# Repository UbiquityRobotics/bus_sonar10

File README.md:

# bus_sonar10

The Sonar10 board is used to drive up to 10 HC-SR04
sonar modules.

Currently, everything is located in the `rev_a` directory.

## Revision A

The revision A schematic is available as either
`bus_sonar10.pdf` or as `bus_sonar10.svg`.

Logic ground comes in on N1 (pins 3 and 4).  Logic
power comes in on N1 (pins 1 and 2.)  The logic power
is routed to C1, U2 (a LM2940-5.0), C4, C5, and R1.
The C4/R1 series combination is used to bring the
ESR of C5 to less than 1 ohm as required by the
LM2940 spec. sheet.  Capacitors C6, C7, C8, C9, and
C11 provide filter capacitors for the various IC's.

The MCP2562 CAN bus transceiver (U3) is connected to
CANH (N1 pin 5) and CANL (N1 pin 6).  In addition,
R6 and J1 can be used to enable a 120 ohm CAN bus
termination resistor.  VIO (U3 pin 5) is connected
to 5V since all digital signals on this board are
running at 5V.

The AND gate at U1A is used to or the signals from
the MCP2562 TXD (U3 pin 1) with the TXD signal on
the 3.3V FTDI USB serial cable (N2 pin 4).  R4 is
a 100K ohm pull resistor that pulls serial cable
high if no serial cable is plugged in.  (There should
be a similar 100K pull-up resistor on the MCP2662
to pull it high if the MCP2562 CAN bus transceiver
is not plugged in.  It was accidently left out.)
The output of the 74HCT08 and gate is directed to
RXD (U4 pin 2) of the ATmega328P.  The 74HCT08 is
used to level shift from 3.3V on the serial cable
up to 5V output on U1A.  (Note: in Rev. A the TXD
and RXD pins on U3 are accidentally swapped.)  Lastly,
the TXD output from the processor is sent to the R2/R3
voltage divider that takes the 0-5V signal down to 0-3V.

One other comment about the serial cable.  If a 5V FTDI
serial cable gets plugged into N2, nothing bad happens
because U1 has 5V tolerant inputs.

The reset signal is derived from RTS on the serial cable
(N2 pin 6.)  Normally, RTS on the serial cable idles
at 3.3V high, which is buffered through AND gate U1B
to 5V.  The othe end of C10 is pulled up to 5V through
10K resistor (R7).  Since both ends of C10 are at 5V,
C10 is discharged and has 0V across it.  When RTS goes
low, the output of U1B goes low.  This immediately pulls
the #RESET line low and that resets the processor on
its #RESET line (U4 pin 1).  Now R7 has 5V across it
and it starts to charge C10 up to 5V.  When downloading
is done, The serial cable signal RTS goes back high again.
This the causes the U1B AND output to go high (5V).
This causes the other end of C10 to attempt to pull
the #RESET line up to 10V (since C10 has 5V across it.)
Luckily the Schottky diode D1 to clamp the voltage
on the #RESET line to 5.2V and rapidly discharge C10
again.  Lastly, the button SW1 can be used to trigger
a reset as well.

(There was a theory that the AVR counter/timers could
be used to time the width of a pulse.  For this reason,
all sonar echos were run into the input pins of
5 (OC2B), 11 (OC0B), 12 (OC0A), 15 (OC1A), 16 (OC1B),
and 17 (OC2A).  Alas, this theory turned out to be
false.)

Order to support 10 sonars, pairs of echo return signals
from the HC-SR04 modules are combined using the 74HCT32
quad OR gate U5.  By using these 4 OR gates, the 10
sonar echos are directed to 6 input pins.  This is good
because 6 input pins are all that is available.

All the connections are summerized in the table below:
<BlockQuote>
  <Table Border="1">
    <TR>
      <TH RowSpan="2">Sonar</TH>
      <TH ColSpan="4">Trigger</TH>
      <TH ColSpan="7">Echo</TH>
    </TR><TR>
      <TH>Pin</TH>
      <TH>Arduino</TH>
      <TH>Port-Bit </TH>
      <TH>Conn-Pin</TH>
      <TH>Pin</TH>
      <TH>Arduino</TH>
      <TH>Counter</TH>
      <TH>Port-Bit</TH>
      <TH>PCINT</TH>
      <TH>Conn-Pin</TH>
    </TR><TR>
      <TD>0</TD>
      <TD>24</TD>
      <TD>A1</TD>
      <TD>PC1</TD>
      <TD>N3-5</TD>
      <TD RowSpan="2">15</TD>
      <TD RowSpan="2">D9</TD>
      <TD RowSpan="2">OC1A</TD>
      <TD RowSpan="2">PB1</TD>
      <TD RowSpan="2">PCINT1</TD>
      <TD>N3-3</TD>
    </TR><TR>
      <TD>1</TD>
      <TD>19</TD>
      <TD>D13</TD>
      <TD>PB5</TD>
      <TD>N3-13</TD>
      <TD>N3-11</TD>
    </TR><TR>
      <TD>2</TD>
      <TD>23</TD>
      <TD>A0</TD>
      <TD>PC0</TD>
      <TD>N3-21</TD>
      <TD>12</TD>
      <TD>D6</TD>
      <TD>OC0A</TD>
      <TD>PD6</TD>
      <TD>PCINT22</TD>
      <TD>N3-19</TD>
    </TR><TR>
      <TD>3</TD>
      <TD>18</TD>
      <TD>D12</TD>
      <TD>PB4</TD>
      <TD>N3-29</TD>
      <TD RowSpan="2">11</TD>
      <TD RowSpan="2">D5</TD>
      <TD RowSpan="2">OC0B</TD>
      <TD RowSpan="2">PD5</TD>
      <TD RowSpan="2">PCINT21</TD>
      <TD>N3-27</TD>
    </TR><TR>
      <TD>4</TD>
      <TD>14</TD>
      <TD>D8</TD>
      <TD>PB0</TD>
      <TD>N3-37</TD>
      <TD>N3-35</TD>
    </TR><TR>
      <TD>5</TD>
      <TD>26</TD>
      <TD>A3</TD>
      <TD>PC3</TD>
      <TD>N4-5</TD>
      <TD RowSpan="2">17</TD>
      <TD RowSpan="2">D11</TD>
      <TD RowSpan="2">OC2A</TD>
      <TD RowSpan="2">PB3</TD>
      <TD RowSpan="2">PCINT3</TD>
      <TD>N4-3</TD>
    </TR><TR>
      <TD>6</TD>
      <TD>25</TD>
      <TD>A2</TD>
      <TD>PC2</TD>
      <TD>N4-13</TD>
      <TD>N4-11</TD>
    </TR><TR>
      <TD>7</TD>
      <TD>13</TD>
      <TD>D7</TD>
      <TD>PD7</TD>
      <TD>N4-21</TD>
      <TD>16</TD>
      <TD>D10</TD>
      <TD>OC1B</TD>
      <TD>PB2</TD>
      <TD>PCINT2</TD>
      <TD>N4-19</TD>
    </TR><TR>
      <TD>8</TD>
      <TD>6</TD>
      <TD>D4</TD>
      <TD>PD4</TD>
      <TD>N4-29</TD>
      <TD RowSpan="2">5</TD>
      <TD RowSpan="2">D3</TD>
      <TD RowSpan="2">OC2B</TD>
      <TD RowSpan="2">PD3</TD>
      <TD RowSpan="2">PCINT19</TD>
      <TD>N4-27</TD>
    </TR><TR>
      <TD>9</TD>
      <TD>4</TD>
      <TD>D2</TD>
      <TD>PD2</TD>
      <TD>N4-37</TD>
      <TD>N4-35</TD>
    </TR>
  </Table>
</BlockQuote>

### Issues

* The TXD and RXD pins on the MCP2562 (U3 pins 1 and 4) are
  swapped. [x]

* It would be nice to have an LED that can be blinked. [x]

* Tie unused inputs of U1 to one rail or the other. [x]

* Put a 100K pull up on U1A (pin 1) to deal with MCP2652 not
  being plugged in.. [x]

* Think about finding an extra pin for STBY on the MCP2652
  rather than just grounding it. [x]

* References for D1 and R7 are transposed. [x]

### Rev. C

- No ISP connector.

## Software

The software is developed using the arduino-mk package.
You may have to edit the Makefile if you are not using
a standard Ubuntu configuration and/or an 3.3V FTDI USB
to serial cable.

The software is in `bus_sonar10.ino`.

To build the code:

        make

To upload the code to bus_sonar10 over the FTDI serial cable:

        make upload

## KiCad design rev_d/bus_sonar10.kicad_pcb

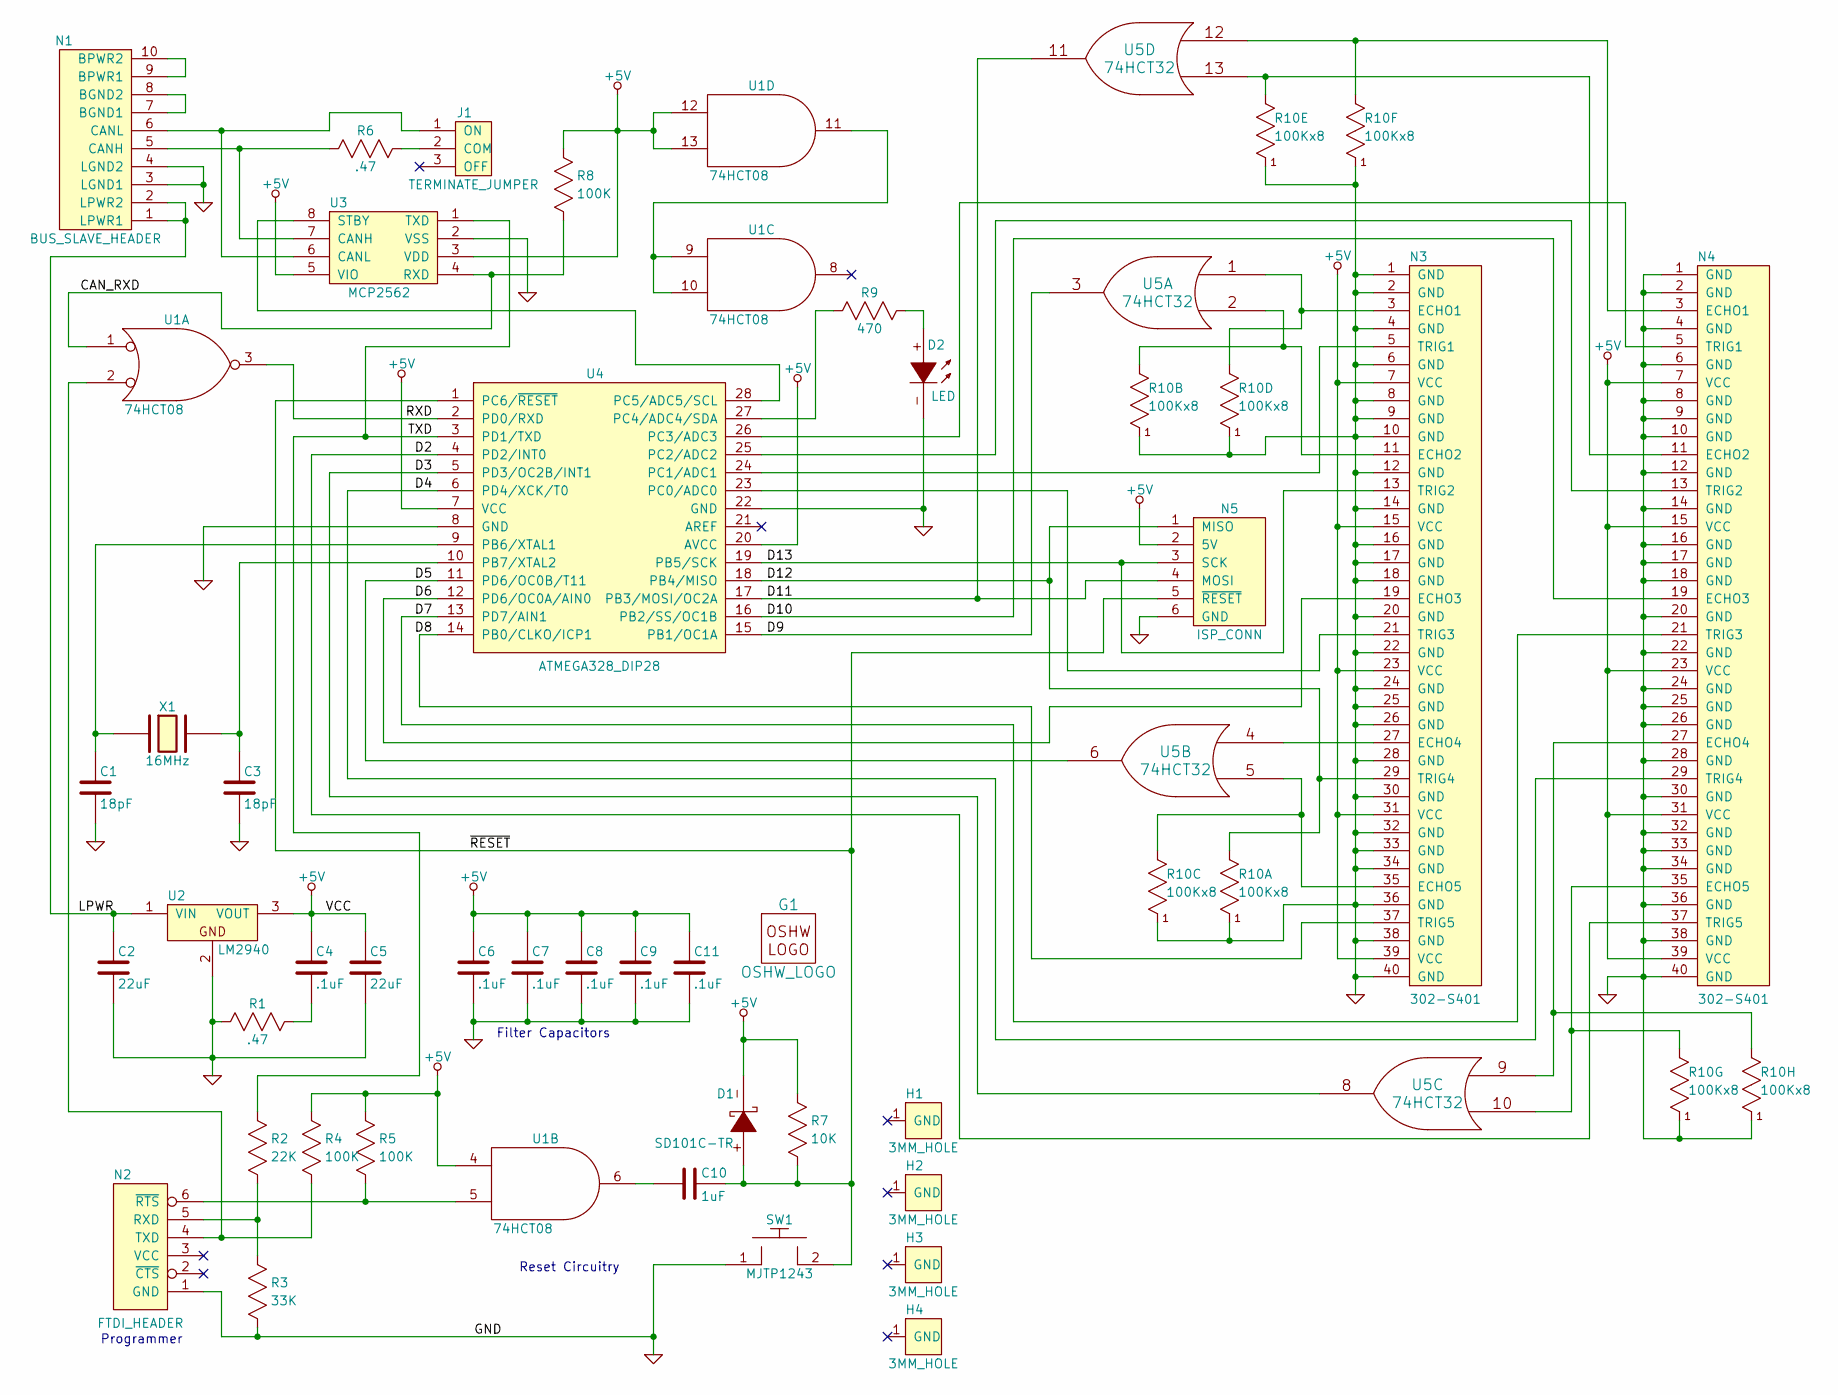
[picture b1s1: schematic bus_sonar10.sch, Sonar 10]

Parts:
C1, C3: 18pF; Capacitor3MMDiscRM2.5
C2, C5: 22uF; Capacitor4x3RM2-5_RevB
C4, C6, C7, C8, C9, C11: .1uF; Capacitor3MMDiscRM2.5
C10: 1uF; Capacitor3MMDiscRM2.5
D1: SD101C-TR; Diode_DO-41_SOD81_Horizontal_RM10
D2: LED; T1_LED
G1: OSHW_LOGO; OSHW_LOGO_400mil
H1, H2, H3, H4: 3MM_HOLE; MountingHole_3mm
J1: TERMINATE_JUMPER; Pin_Header_Straight_1x03
N1: BUS_SLAVE_HEADER; Pin_Header_Straight_2x05_Shrouded
N2: FTDI_HEADER; Pin_Header_Straight_1x06
N3, N4: 302-S401; Pin_Header_Straight_2x20_Shrouded
N5: ISP_CONN; Pin_Header_Straight_2x03
R1, R6: .47; Resistor_Horizontal_400
R2: 22K; Resistor_Horizontal_400
R3: 33K; Resistor_Horizontal_400
R4, R5, R8: 100K; Resistor_Horizontal_400
R7: 10K; Resistor_Horizontal_400
R9: 470; Resistor_Horizontal_400
R10: 100Kx8; Pin_Header_Straight_1x09
SW1: MJTP1243; Button_6.5MM
U1: 74HCT08; DIP-14__300
U2: LM2940; TO-220_Neutral123_Horizontal_LargePads
U3: MCP2562; DIP-8__300
U4: ATMEGA328_DIP28; DIP-28__300
U5: 74HCT32; DIP-14__300
X1: 16MHz; Crystal_HC49-U_Vertical

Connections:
/CAN_RXD: R8.1, U1.1, U3.4 (RXD)
/D2: N4.37 (TRIG5), U4.4 (PD2/INT0)
/D3: U4.5 (PD3/OC2B/INT1), U5.8
/D4: N4.29 (TRIG4), U4.6 (PD4/XCK/T0)
/D5: U4.11 (PD6/OC0B/T11), U5.6
/D6: N3.19 (ECHO3), U4.12 (PD6/OC0A/AIN0)
/D7: N4.21 (TRIG3), U4.13 (PD7/AIN1)
/D8: N3.37 (TRIG5), U4.14 (PB0/CLKO/ICP1)
/D9: U4.15 (PB1/OC1A), U5.3
/D10: N4.19 (ECHO3), U4.16 (PB2/SS/OC1B)
/D11: N5.4 (MOSI), U4.17 (PB3/MOSI/OC2A), U5.11
/D12: N3.29 (TRIG4), N5.1 (MISO), R10.2, U4.18 (PB4/MISO)
/D13: N3.13 (TRIG2), N5.3 (SCK), U4.19 (PB5/SCK)
/LPWR: C2.1, N1.1 (LPWR1), N1.2 (LPWR2), U2.1 (VIN)
/RXD: U1.3, U4.2 (PD0/RXD)
/TXD: R2.2, U3.1 (TXD), U4.3 (PD1/TXD)
/~RESET: C10.2, D1.+, N5.5 (~RESET), R7.1, SW1.2, U4.1 (PC6/~RESET)
GND: C1.2, C2.2, C3.2, C5.2, C6.2, C7.2, C8.2, C9.2, C11.2, D2.-, N1.3 (LGND1), N1.4 (LGND2), N2.1 (GND), N3.1 (GND), N3.2 (GND), N3.4 (GND), N3.6 (GND), N3.8 (GND), N3.9 (GND), N3.10 (GND), N3.12 (GND), N3.14 (GND), N3.16 (GND), N3.17 (GND), N3.18 (GND), N3.20 (GND), N3.22 (GND), N3.24 (GND), N3.25 (GND), N3.26 (GND), N3.28 (GND), N3.30 (GND), N3.32 (GND), N3.33 (GND), N3.34 (GND), N3.36 (GND), N3.38 (GND), N3.40 (GND), N4.1 (GND), N4.2 (GND), N4.4 (GND), N4.6 (GND), N4.8 (GND), N4.9 (GND), N4.10 (GND), N4.12 (GND), N4.14 (GND), N4.16 (GND), N4.17 (GND), N4.18 (GND), N4.20 (GND), N4.22 (GND), N4.24 (GND), N4.25 (GND), N4.26 (GND), N4.28 (GND), N4.30 (GND), N4.32 (GND), N4.33 (GND), N4.34 (GND), N4.36 (GND), N4.38 (GND), N4.40 (GND), N5.6 (GND), R1.1, R3.1, R10.1, SW1.1, U1.7 (GND), U2.2, U3.2 (VSS), U4.8 (GND), U4.22 (GND), U5.7 (GND)
unnamed: C1.1, U4.9 (PB6/XTAL1), X1.1
unnamed: C3.1, U4.10 (PB7/XTAL2), X1.2
unnamed: C4.2, R1.2
unnamed: C10.1, U1.6
unnamed: D2.+, R9.2
unnamed: J1.1 (ON), N1.6 (CANL), U3.6 (CANL)
unnamed: J1.2 (COM), R6.2
unnamed: N1.5 (CANH), R6.1, U3.7 (CANH)
unnamed: N1.7 (BGND1), N1.8 (BGND2)
unnamed: N1.9 (BPWR1), N1.10 (BPWR2)
unnamed: N2.4 (TXD), R4.1, U1.2
unnamed: N2.5 (RXD), R2.1, R3.2
unnamed: N2.6 (~RTS), R5.1, U1.5
unnamed: N3.3 (ECHO1), R10.5, U5.1
unnamed: N3.5 (TRIG1), U4.24 (PC1/ADC1)
unnamed: N3.11 (ECHO2), R10.3, U5.2
unnamed: N3.21 (TRIG3), U4.23 (PC0/ADC0)
unnamed: N3.27 (ECHO4), U5.4
unnamed: N3.35 (ECHO5), R10.4, U5.5
unnamed: N4.3 (ECHO1), R10.7, U5.12
unnamed: N4.5 (TRIG1), U4.26 (PC3/ADC3)
unnamed: N4.11 (ECHO2), R10.6, U5.13
unnamed: N4.13 (TRIG2), U4.25 (PC2/ADC2)
unnamed: N4.27 (ECHO4), R10.9, U5.9
unnamed: N4.35 (ECHO5), R10.8, U5.10
unnamed: R9.1, U4.27 (PC4/ADC4/SDA)
unnamed: U1.9, U1.10, U1.11
unnamed: U3.8 (STBY), U4.28 (PC5/ADC5/SCL)
VCC: C4.1, C5.1, C6.1, C7.1, C8.1, C9.1, C11.1, D1.-, N3.7 (VCC), N3.15 (VCC), N3.23 (VCC), N3.31 (VCC), N3.39 (VCC), N4.7 (VCC), N4.15 (VCC), N4.23 (VCC), N4.31 (VCC), N4.39 (VCC), N5.2 (5V), R4.2, R5.2, R7.2, R8.2, U1.4, U1.12, U1.13, U1.14 (VCC), U2.3 (VOUT), U3.3 (VDD), U3.5 (VIO), U4.7 (VCC), U4.20 (AVCC), U5.14 (VCC)

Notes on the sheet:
Filter Capacitors
Reset Circuitry
Programmer

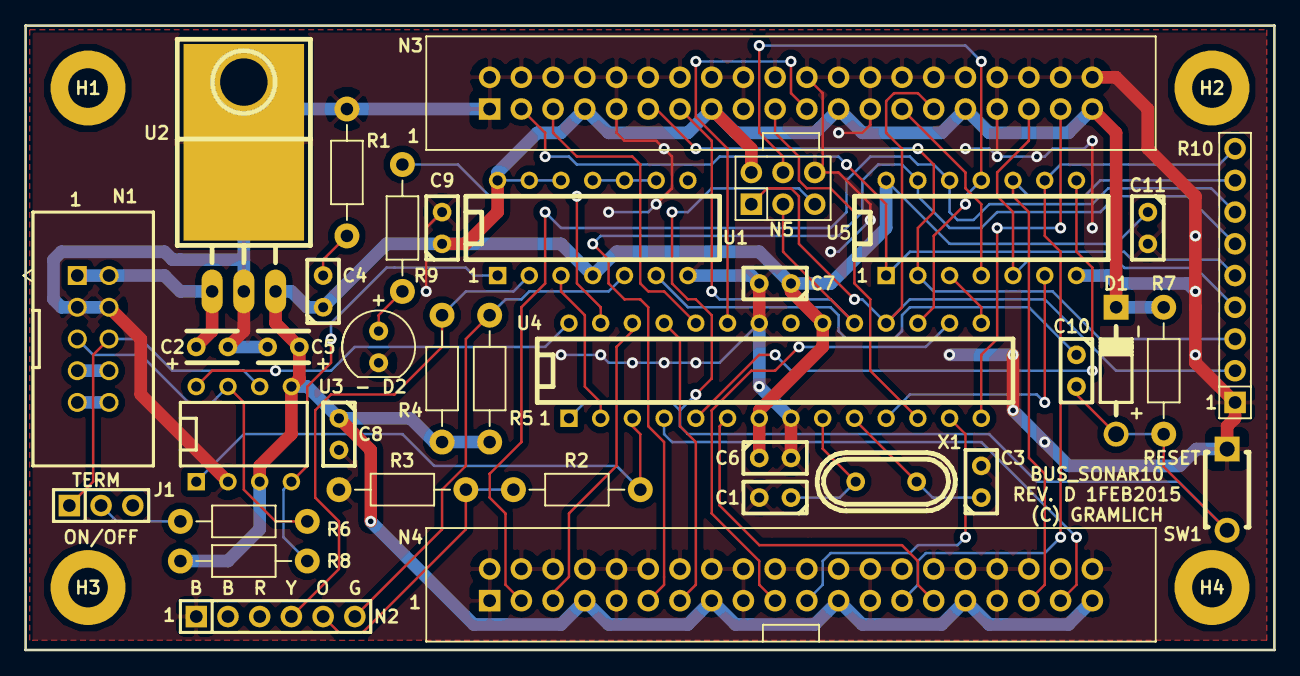
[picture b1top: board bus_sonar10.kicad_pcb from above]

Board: 2 copper layers, 100.0 x 50.0 mm, 41 parts (1 on the bottom side), 47 nets.

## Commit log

2014-08-17 Started from a clone of bus_bridge_encoders_sonar.
2014-08-18 Finnished laying out Rev. A
2014-08-18 Added silkscreen outline.
2014-08-18 CRYSTAL=>16MHz
2014-09-26 Added bus_sonar10.ino and Makefile. Updated README.md.
2014-09-26 Fixing table.
2014-09-26 Fixed table some more.
2014-09-26 Fixed a formatting error in READEM.md
2014-09-26 Fixed some more formatting errors.
2014-10-04 Updated fp-lib-table for Rev. A, but did not load the new net into the PCB. This is in preparation for making a Rev. B clone of Rev. A.
2014-10-04 Cloned Rev. B from Rev. A.
2014-10-04 Imported the new network into Rev. B.
2014-10-04 Got Rev. B in pretty good shape.
2014-10-05 Added Kurt's modifications for bus_sonar10.ino
2014-10-17 Checked in gerbers for Rev. B. Cloned Rev. B for Rev. C
2014-10-20 Wrapped up Rev. C
2014-10-20 Made sure that Rev. C was up to date.
2014-10-21 Changed 8 100K's to 8 100Kx8's.
2015-01-28 Missing IPS connector.
2015-02-01 Cloned Rev. C to Rev. D
2015-02-01 Added ISP connector.
2015-02-03 Mounting holes are now electrically isolated.
2015-02-13 Split 22uF capacitor into aluminum and tantalum.
2015-05-29 Configured a simple framework for the sonars. This code only compiles and has not been tested.
2015-06-03 Copied over code from bus_bridge_encoders_sonar and changed it to compile and 'work' for bus_sonar10. Most of the code is silly since it references stuff on the bus_bridge_encoders_sonar board.
2015-06-04 Removed lots of unnecessary code left over from bus_bridge_encoders_sonar.
2015-06-04 Removed Bus_Sonar10.h
2015-06-04 Got bus_sonar10 to return ficticious sonar data over the bus.
2015-06-04 Removed unused and unneed encoder registers from bus_sonar10.
2015-06-07 Refactored the code so that Sonar.{h,cpp} no longer needs RAB_Sonar{h,cpp}. This touched a bunch of files.
2015-06-08 Started adding Sonar_Queue objects.
2015-06-08 Removed concept of unit number for sonars.
2015-06-08 Added Sonar_Queue object to Sonar.
2015-06-08 Switch Sonar() constructor to use bit numbers rather than bit masks for argument values.
2015-06-09 More prep. work for Sonar_Queue's.
2015-06-09 Sonar_Controller=>Sonars_Controller. Add sonars_schedule argument to constructor.
2015-06-10 More code cleanup.
2015-06-11 Started doxygen documentation for Sonar. Removed an argument from Sonar() constructor.
2015-06-12 Added sonar change mask to indicate whic sonar distances have changed.
2015-06-14 Fixed Sonar so that it does not screw up on sonars.
